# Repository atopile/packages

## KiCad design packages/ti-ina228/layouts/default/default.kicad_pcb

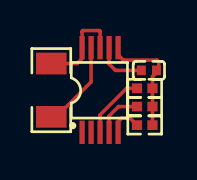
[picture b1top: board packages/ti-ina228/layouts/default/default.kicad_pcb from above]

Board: 2 copper layers, 6 parts (0 on the bottom side), 7 nets.

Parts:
C1: 100nF; C0402
R1: 150mΩ; R1206
R2, R3, R4: 10kΩ; R0402
U1: VSSOP-10_L3.0-W3.0-P0.50-LS4.9-BL

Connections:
ALERT: R4.1, U1.3
SCL: R2.1, U1.5
SDA: R3.1, U1.4
hv: C1.1, R2.2, R3.2, R4.2, U1.6
lv: C1.2, U1.1, U1.2, U1.7
power_in_P: R1.1, U1.8, U1.10
power_out_N: R1.2, U1.9

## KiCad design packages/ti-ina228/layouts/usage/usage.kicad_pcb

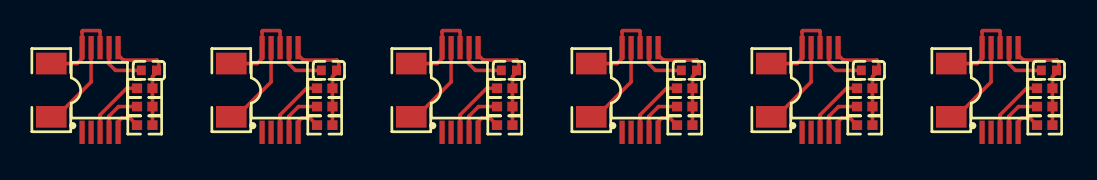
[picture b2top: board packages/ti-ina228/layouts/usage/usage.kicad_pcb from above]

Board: 2 copper layers, 36 parts (0 on the bottom side), 32 nets.

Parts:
C1, C2, C3, C4, C5, C6: 100nF; C0402
R1, R2, R4, R5, R7, R8, R10, R11, R13, R14, R16, R17, R19, R20, R21, R22, R23, R24: 10kΩ; R0402
R3, R6: 80mΩ; R1206
R9: 16mΩ; R1206
R12, R18: 330mΩ; R1206
R15: 30mΩ; R1206
U1, U2, U3, U4, U5, U6: VSSOP-10_L3.0-W3.0-P0.50-LS4.9-BL

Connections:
ALERT: R19.1, U1.3
SCL: R1.1, U1.5
SDA: R2.1, U1.1, U1.4
battery_in_P: R3.1, U1.8, U1.10
battery_out_N: R3.2, U1.9
hv: C1.1, C2.1, C3.1, C4.1, C5.1, C6.1, R1.2, R2.2, R4.2, R5.2, R7.2, R8.2, R10.2, R11.2, R13.2, R14.2, R16.2, R17.2, R19.2, R20.2, R21.2, R22.2, R23.2, R24.2, U1.6, U2.2, U2.6, U3.6, U4.1, U4.6, U5.6, U6.6
lv: C1.2, C2.2, C3.2, C4.2, C5.2, C6.2, U1.2, U1.7, U2.1, U2.7, U3.1, U3.7, U4.2, U4.7, U5.1, U5.7, U6.1, U6.2, U6.7
main_3v3_in_P: R6.1, U2.8, U2.10
main_3v3_monitor-alert-ALERT: R20.1, U2.3
main_3v3_monitor-i2c-SCL: R4.1, U2.5
main_3v3_monitor-i2c-SDA: R5.1, U2.4
main_3v3_out_N: R6.2, U2.9
motor_monitor-alert-ALERT: R21.1, U3.3
motor_monitor-i2c-SCL: R7.1, U3.2, U3.5
motor_monitor-i2c-SDA: R8.1, U3.4
motor_pwr_in_P: R9.1, U3.8, U3.10
motor_pwr_out_N: R9.2, U3.9
poe_in_P: R12.1, U4.8, U4.10
poe_monitor-alert-ALERT: R22.1, U4.3
poe_monitor-i2c-SCL: R10.1, U4.5
poe_monitor-i2c-SDA: R11.1, U4.4
poe_out_N: R12.2, U4.9
supply_12v_in_P: R15.1, U5.8, U5.10
supply_12v_monitor-alert-ALERT: R23.1, U5.3
supply_12v_monitor-i2c-SCL: R13.1, U5.5
supply_12v_monitor-i2c-SDA: R14.1, U5.2, U5.4
supply_12v_out_N: R15.2, U5.9
usb_5v_in_P: R18.1, U6.8, U6.10
usb_5v_out_N: R18.2, U6.9
usb_monitor-alert-ALERT: R24.1, U6.3
usb_monitor-i2c-SCL: R16.1, U6.5
usb_monitor-i2c-SDA: R17.1, U6.4

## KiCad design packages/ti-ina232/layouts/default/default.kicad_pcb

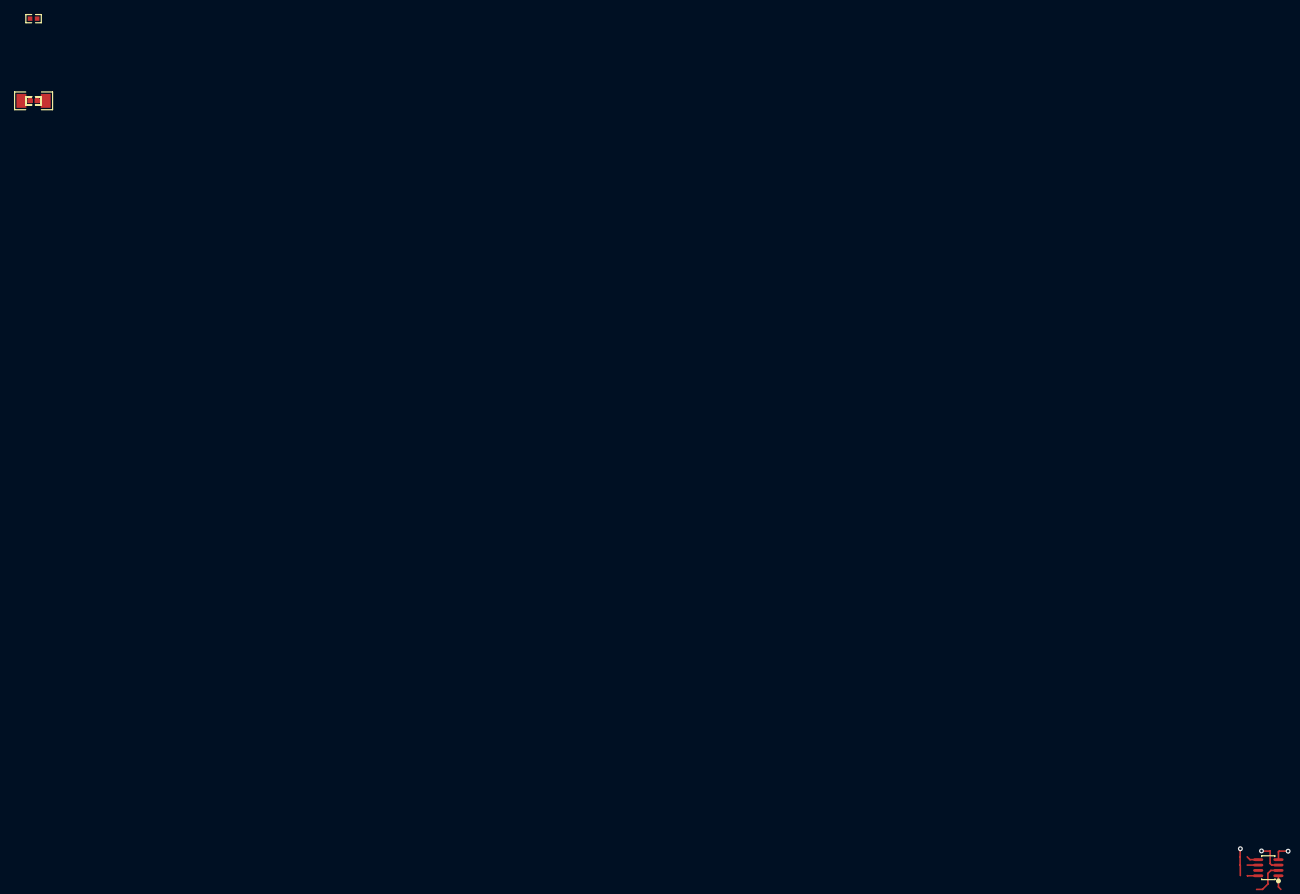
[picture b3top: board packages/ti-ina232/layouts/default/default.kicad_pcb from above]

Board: 2 copper layers, 6 parts (0 on the bottom side), 7 nets.

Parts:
C1: 100nF; C0402
R1, R2, R3: 10kΩ; R0402
R4: 70mΩ; R1206
U1: SOT-23-8_L2.9-W1.6-P0.65-LS2.8-BR

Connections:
ALERT: R3.1, U1.8
SCL: R1.1, U1.5
SDA: R2.1, U1.6
hv: C1.1, R1.2, R2.2, R3.2, U1.4
lv: C1.2, U1.3, U1.7
power_in_P: R4.1, U1.1
power_out_N: R4.2, U1.2

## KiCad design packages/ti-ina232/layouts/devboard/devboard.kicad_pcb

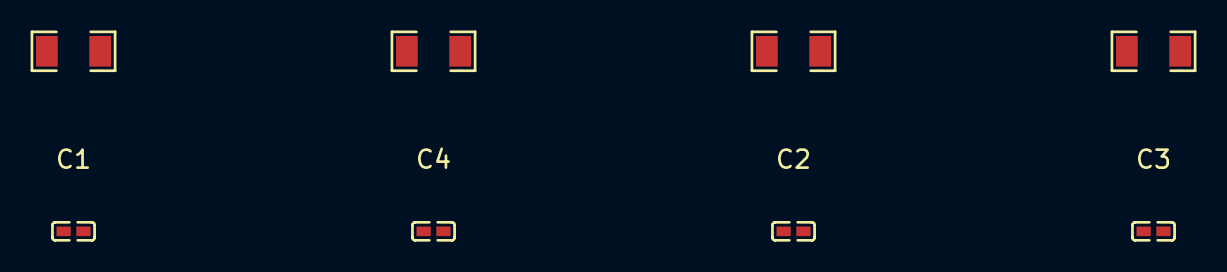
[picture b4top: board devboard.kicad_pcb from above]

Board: 2 copper layers, 8 parts (0 on the bottom side), 2 nets.

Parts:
C1, C2, C3, C4: 100nF ±10% 16V X7R; C0402-b3ef17
R1, R2, R3, R4: 100Ω ±1% 250mW; R1206-bdb864

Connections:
gnd: C1.2, C2.2, C3.2, C4.2
hv: C1.1, C2.1, C3.1, C4.1

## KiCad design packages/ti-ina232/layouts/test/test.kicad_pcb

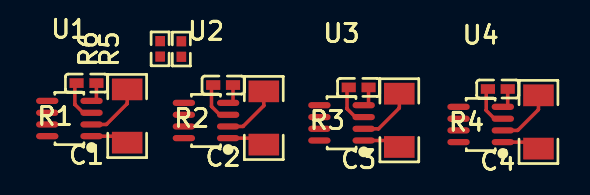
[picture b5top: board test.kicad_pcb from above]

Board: 2 copper layers, 14 parts (0 on the bottom side), 6 nets.

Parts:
C1, C2, C3, C4: 100nF ±10% 16V X7R; C0402
R1: 800mΩ ±1% 250mW; R1206
R2: 70mΩ ±1% 500mW; R1206
R3: 25mΩ ±1% 1W; R1206
R4: 7mΩ ±1% 1W; R1206
R5, R6: 10kΩ ±1% 62.5mW; R0402
U1, U2, U3, U4: SOT-23-8_L2.9-W1.6-P0.65-LS2.8-BR

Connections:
INneg: R1.2, R2.2, R3.2, R4.2, U1.2, U2.2, U3.2, U4.2
INpos: R1.1, R2.1, R3.1, R4.1, U1.1, U2.1, U3.1, U4.1
SCL: R5.1, U1.5, U2.5, U3.5, U4.5, U4.7
SDA: R6.1, U1.6, U2.6, U3.6, U3.7, U4.6
gnd: C1.2, C2.2, C3.2, C4.2, U1.3, U1.7, U2.3, U3.3, U4.3
hv: C1.1, C2.1, C3.1, C4.1, R5.2, R6.2, U1.4, U2.4, U2.7, U3.4, U4.4

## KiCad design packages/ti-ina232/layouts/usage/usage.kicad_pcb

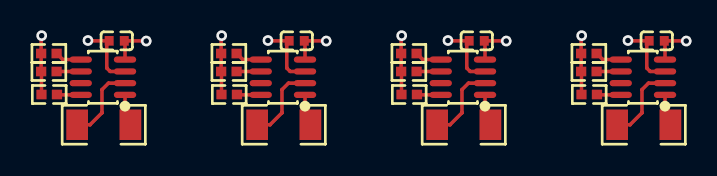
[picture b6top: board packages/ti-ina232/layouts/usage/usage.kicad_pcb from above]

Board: 2 copper layers, 24 parts (0 on the bottom side), 19 nets.

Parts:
C1, C2, C3, C4: 100nF; C0402
R1, R2, R3, R5, R6, R7, R9, R10, R11, R13, R14, R15: 10kΩ; R0402
R4: 140mΩ; R1206
R8: 70mΩ; R1206
R12: 14mΩ; R1206
R16: 7mΩ; R1206
U1, U2, U3, U4: SOT-23-8_L2.9-W1.6-P0.65-LS2.8-BR

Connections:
ALERT: R1.1, U1.8
SCL: R2.1, U1.5
SDA: R3.1, U1.6
hv: C1.1, C2.1, C3.1, C4.1, R1.2, R2.2, R3.2, R5.2, R6.2, R7.2, R9.2, R10.2, R11.2, R13.2, R14.2, R15.2, U1.4, U2.4, U2.7, U3.4, U4.4
load1_N: R4.2, U1.2
load2_N: R8.2, U2.2
load3_N: R12.2, U3.2
load4_N: R16.2, U4.2
lv: C1.2, C2.2, C3.2, C4.2, U1.3, U1.7, U2.3, U3.3, U4.3
sensor2-alert-ALERT: R5.1, U2.8
sensor2-i2c-SCL: R6.1, U2.5
sensor2-i2c-SDA: R7.1, U2.6
sensor3-alert-ALERT: R9.1, U3.8
sensor3-i2c-SCL: R10.1, U3.5
sensor3-i2c-SDA: R11.1, U3.6, U3.7
sensor4-alert-ALERT: R13.1, U4.8
sensor4-i2c-SCL: R14.1, U4.5, U4.7
sensor4-i2c-SDA: R15.1, U4.6
supply_P: R4.1, R8.1, R12.1, R16.1, U1.1, U2.1, U3.1, U4.1

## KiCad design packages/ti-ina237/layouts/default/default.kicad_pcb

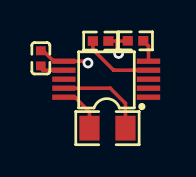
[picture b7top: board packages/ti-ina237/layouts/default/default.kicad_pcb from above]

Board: 2 copper layers, 5 parts (0 on the bottom side), 6 nets.

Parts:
C1: 0F; C0402
R1, R2: 10000Ω; R0402
R3: 0.15Ω; R0805
U1: VSSOP-10_L3.0-W3.0-P0.50-LS4.9-BL

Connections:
INneg_N: R3.2, U1.9
INpos_P: R3.1, U1.10
SCL: R1.1, U1.5
SDA: R2.1, U1.4
hv: C1.1, R1.2, R2.2, U1.6
lv: C1.2, U1.1, U1.2, U1.7
